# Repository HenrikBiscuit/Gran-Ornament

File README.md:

# Gran Ornament

A small, rechargeable, two-sided LED Christmas ornament. Twenty warm-white LEDs in seven channels (three rows per side and a shared star) play slow and calm light: steady high or low, a slow breath, or a flickering candle. One button turns it on, it fades in and out, switches itself off after four hours, and sleeps quietly between Christmases.

Made by hand in small batches in Denmark. This repository is the open build log: hardware, firmware, and the notes behind the decisions.

> **Status:** 🛠 Prototyping. First batch of Rev 1 boards ordered. Firmware runs on a dev board: four light modes, button, Standby, auto-off, battery compensation and low-battery cutoff. Nothing here is production-ready yet.

<!-- Add a photo here once you have one:  -->

## Using it

| Do this | What happens |
|---|---|
| Press the button | It fades in, in the mode it had last time (high if the battery has been disconnected) |
| Short press | Next mode: high → low → breathe → candle |
| Hold for 1.5 s | It fades out and switches off |
| Leave it on | It fades out and switches off by itself after 4 hours |
| Battery runs low | It fades out, pulses softly three times ("charge me") and switches off |
| Charge | USB-C |

The brightness stays the same while the battery drains, down to the 3.6 V cutoff.

## What's in here

| Folder | Contents |
|---|---|
| [`hardware/`](hardware/) | KiCad project, datasheet links, fabrication outputs (Gerbers, BOM, CPL). Each ordered revision is a [Release](../../releases), e.g. [`hw-v1`](../../releases/tag/hw-v1) |
| [`firmware/`](firmware/) | STM32G030 firmware. Runs on the dev board for now. How to build, test and lint: [`firmware/README.md`](firmware/README.md) |
| [`firmware/tests/`](firmware/tests/) | Host-side GoogleTest tests for the firmware logic, run in CI and by the pre-push gate |
| [`docs/`](docs/) | Design decisions, power budget, pinout, bring-up notes, images |
| `production/` | Programming and test process for each batch (not created yet) |
| [`CHANGELOG.md`](CHANGELOG.md) | What changed, per hardware and firmware version |

## Key parts (current choices)

| Function | Part | Notes |
|---|---|---|
| MCU | STM32G030F6P6 | Cortex-M0+, 64 MHz, 32 KB flash, 8 KB RAM, TSSOP-20 |
| LEDs | 20 × XL-1608WWC-06 | Warm white, 1608 metric (0603 imperial) |
| Charger | MCP73831 (SOT-23-5) | Linear single-cell Li-ion/LiPo charger, 4.20 V variant, 100 mA, USB-C input |
| Protection | DW01A + FS8205A | Over-discharge, over-charge and over-current protection on the board |
| Regulator | TPS7A0233 | 3.3 V LDO, ~25 nA quiescent current |
| Button | Alps SKRTLAE010 | Side-push SMD tact switch |
| Battery | Single-cell LiPo, 250 mAh planned | Cell size *TBD* (DD-002) |

Full design rationale: [`docs/design-decisions.md`](docs/design-decisions.md)

## Design goals

1. **Works next Christmas.** Every choice favours longevity: deep sleep, over-discharge protection, a battery that survives 11 months in a box.
2. **Calm light.** Gamma-corrected, high-resolution, flicker-free PWM. Nothing jumpy, nothing "disco".
3. **Safe to hang where children and pets are.** LiPo safety and robustness are requirements.
4. **Buildable by one or two people** in batches of about 150.

## Roadmap

- [x] Initial KiCad schematic
- [x] Dev board bring-up: PWM on all 7 channels, button, Standby and wake
- [x] Light modes: high, low, breathe, candle
- [x] Battery measurement, brightness compensation and low-battery cutoff (DD-011)
- [x] Fade in and out when switching on and off
- [x] PCB layout and fabrication files (Rev 1)
- [x] First batch of Rev 1 boards ordered
- [ ] Measure Standby current on the dev board
- [ ] Gamma-corrected brightness (smooth fades at the dim end)
- [ ] Stay off when a battery is first connected (saves ~100 mAh, see the power budget)
- [ ] VDD via VREFINT (battery reading stays accurate below ~3.4 V)
- [ ] First prototype boards (Rev 1) built and brought up
- [ ] Power budget measured against calculated
- [ ] Production test jig
- [ ] Compliance groundwork (CE, GPSR, Battery Regulation)

Open tasks are tracked in [Issues](../../issues).

## Licence

Gran Ornament is **source-available for non-commercial use**. You're welcome to build one for yourself, as a gift, or with a school or makerspace, and to share improvements.

**Selling it requires permission.** That covers selling assembled ornaments, kits, or boards made from these files. Get in touch at *henrik@smitt.dk* and we'll work something out.

| What | Licence |
|---|---|
| Hardware (`hardware/`), documentation and images (`docs/`) | [CC BY-NC-SA 4.0](LICENSE-CC-BY-NC-SA) |
| Firmware (`firmware/`) | [PolyForm Noncommercial 1.0.0](LICENSE) |

The name "Gran Ornament" and any logo are not covered by these licences. Please don't use them for your own builds.

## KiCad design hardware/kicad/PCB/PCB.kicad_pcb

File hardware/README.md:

# Hardware

## Layout

| Path | What goes here |
|---|---|
| `kicad/` | The KiCad project (`.kicad_pro`, `.kicad_sch`, `.kicad_pcb`) plus project-local symbol and footprint libraries |
| `kicad/lib/` | Custom symbols (`.kicad_sym`) and footprints (`.pretty/`) used by this project only |
| `fabrication/<rev>/` | Exported Gerbers, drill files, BOM and CPL for each board revision sent to the assembler |
| `datasheets/` | Links to the datasheets of every part on the board |

## Revisions

| Rev | Date | Status | Notes |
|---|---|---|---|
| Rev 1 | 2026-10 | First batch ordered ([`fabrication/Rev1/`](fabrication/Rev1/)) | First design. JLCPCB assembly |

Each revision that is sent to fabrication gets a Git tag (`hw-v1`, `hw-v2`, ...) and a
GitHub Release with the fabrication zip attached, so it is always possible to see exactly
what was built.

## Viewing without KiCad

A PDF export of the schematic lives in `docs/schematic-revX.pdf` (File → Plot in the
schematic editor). Re-export it whenever the schematic changes meaningfully, so visitors
can follow along without installing KiCad.

## Before a design leaves the house

- [ ] ERC clean (or every remaining warning explained in a comment)
- [ ] DRC clean against the assembler's design rules
- [ ] Every part has an LCSC/manufacturer part number field
- [ ] BOM and CPL exported and spot-checked for rotation
- [ ] Title block: revision and date updated, no private address
- [ ] Schematic PDF exported to `docs/`
- [ ] Tagged `hw-vX` and fabrication zip attached to a Release

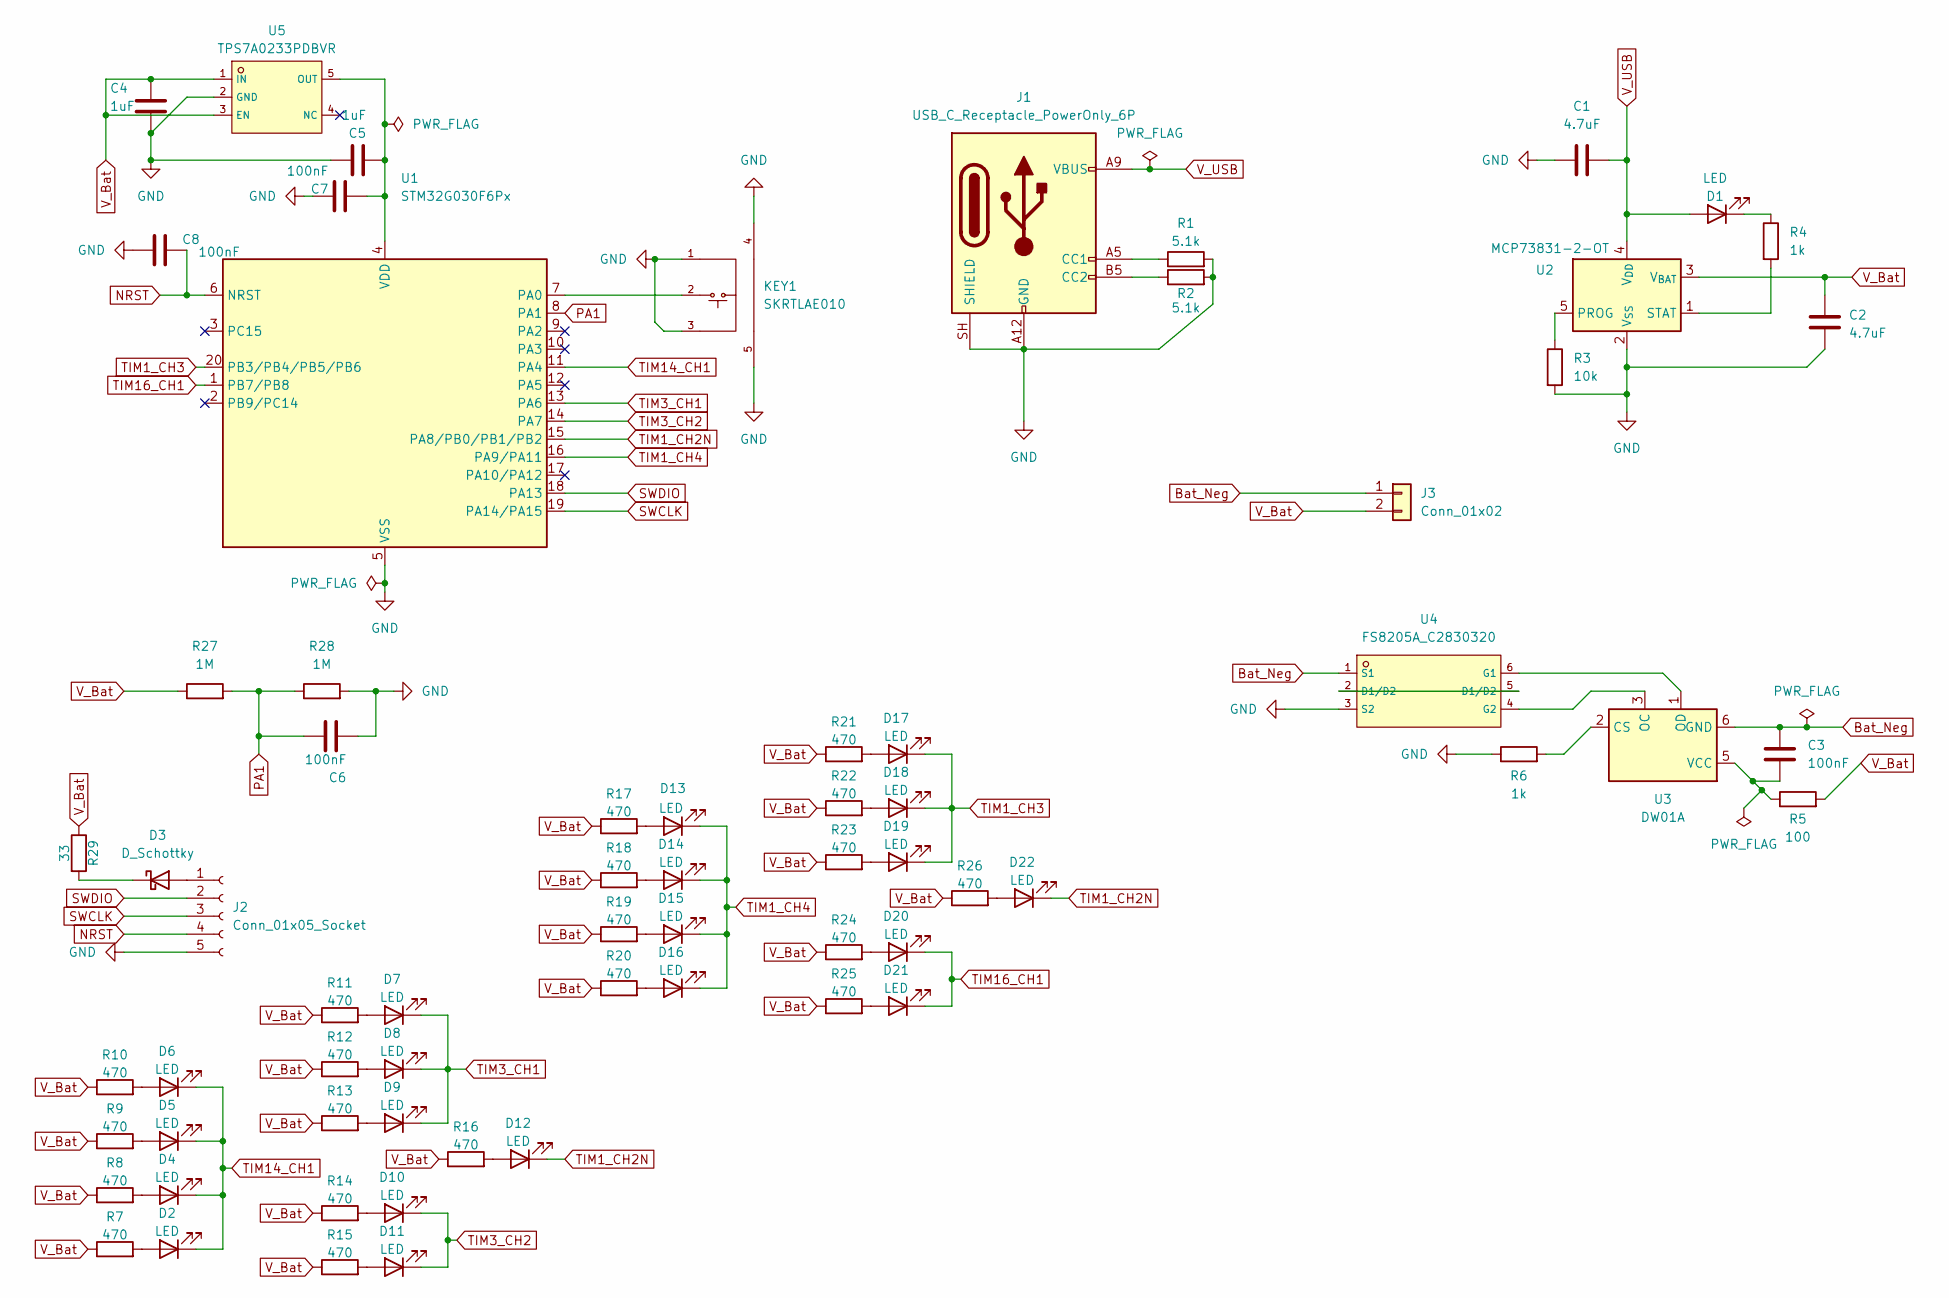
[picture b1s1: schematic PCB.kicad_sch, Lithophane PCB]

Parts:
C1, C2: 4.7uF; C_0603_1608Metric; LCSC C19666
C3, C6, C7, C8: 100nF; C_0603_1608Metric; LCSC C1591
C4, C5: 1uF; C_0603_1608Metric; LCSC C15849
D1: LED; D_0603_1608Metric; LCSC C2286
D2, D4, D5, D6, D7, D8, D9, D10, D11, D12, D13, D14, D15, D16, D17, D18, D19, D20, D21, D22: LED; D_0603_1608Metric; LCSC C965810
D3: D_Schottky; D_SOD-123; LCSC C8598
J1: USB_C_Receptacle_PowerOnly_6P; USB_C_Receptacle_GCT_USB4125-xx-x-0190_6P_TopMnt_Horizontal; LCSC C456012
J2: Conn_01x05_Socket; HDR-SMD_5P-P2.54-H-M-W12.8-N; LCSC C46061678
J3: Conn_01x02; Molex_PicoBlade_53261-0271_1x02-1MP_P1.25mm_Horizontal; LCSC C177225
KEY1: SKRTLAE010; KEY-SMD_SKRTLAE010; LCSC C110293
R1, R2: 5.1k; R_0603_1608Metric; LCSC C23186
R3: 10k; R_0603_1608Metric; LCSC C25804
R4, R6: 1k; R_0603_1608Metric; LCSC C21190
R5: 100; R_0603_1608Metric; LCSC C22775
R7, R8, R9, R10, R11, R12, R13, R14, R15, R16, R17, R18, R19, R20, R21, R22, R23, R24, R25, R26: 470; R_0603_1608Metric; LCSC C23179
R27, R28: 1M; R_0603_1608Metric; LCSC C22935
R29: 33; R_0603_1608Metric; LCSC C23140
U1: STM32G030F6Px; TSSOP-20_4.4x6.5mm_P0.65mm; LCSC C529330
U2: MCP73831-2-OT; SOT-23-5; LCSC C424093
U3: DW01A; SOT-23-6; LCSC C351410
U4: FS8205A_C2830320; SOT-23-6_L2.9-W1.6-P0.95-LS2.8-BR; LCSC C2830320
U5: TPS7A0233PDBVR; SOT-23-5_L2.9-W1.6-P0.95-LS2.8-BR; LCSC C2887324

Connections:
Bat_Neg: C3.1, J3.1, U3.6 (GND), U4.1 (S1)
GND: C1.1, C2.2, C4.2, C5.1, C6.2, C7.1, C8.2, J1.A12 (GND), J1.B12 (GND), J1.SH (SHIELD), J2.5, KEY1.1, KEY1.3, KEY1.4, KEY1.5, R1.2, R2.2, R3.2, R6.1, R28.2, U1.5 (VSS), U2.2 (V_{SS}), U4.3 (S2), U5.2 (GND)
NRST: C8.1, J2.4, U1.6 (NRST)
unnamed: D1.1 (K), R4.1
unnamed: D2.2 (A), R7.2
unnamed: D3.2 (A), J2.1
unnamed: D3.1 (K), R29.2
unnamed: D4.2 (A), R8.2
unnamed: D5.2 (A), R9.2
unnamed: D6.2 (A), R10.2
unnamed: D7.2 (A), R11.2
unnamed: D8.2 (A), R12.2
unnamed: D9.2 (A), R13.2
unnamed: D10.2 (A), R14.2
unnamed: D11.2 (A), R15.2
unnamed: D12.2 (A), R16.2
unnamed: D13.2 (A), R17.2
unnamed: D14.2 (A), R18.2
unnamed: D15.2 (A), R19.2
unnamed: D16.2 (A), R20.2
unnamed: D17.2 (A), R21.2
unnamed: D18.2 (A), R22.2
unnamed: D19.2 (A), R23.2
unnamed: D20.2 (A), R24.2
unnamed: D21.2 (A), R25.2
unnamed: D22.2 (A), R26.2
unnamed: J1.A5 (CC1), R1.1
unnamed: J1.B5 (CC2), R2.1
unnamed: KEY1.2, U1.7 (PA0)
unnamed: C5.2, C7.2, U1.4 (VDD), U5.5 (OUT)
unnamed: R3.1, U2.5 (PROG)
unnamed: R4.2, U2.1 (STAT)
unnamed: R6.2, U3.2 (CS)
unnamed: U3.3 (OC), U4.4 (G2)
unnamed: U3.1 (OD), U4.6 (G1)
unnamed: C3.2, R5.1, U3.5 (VCC)
unnamed: U4.2 (D1/D2), U4.5 (D1/D2)
PA1: C6.1, R27.2, R28.1, U1.8 (PA1)
SWCLK: J2.3, U1.19 (PA14/PA15)
SWDIO: J2.2, U1.18 (PA13)
TIM1_CH2N: D12.1 (K), D22.1 (K), U1.15 (PA8/PB0/PB1/PB2)
TIM1_CH3: D17.1 (K), D18.1 (K), D19.1 (K), U1.20 (PB3/PB4/PB5/PB6)
TIM1_CH4: D13.1 (K), D14.1 (K), D15.1 (K), D16.1 (K), U1.16 (PA9/PA11)
TIM3_CH1: D7.1 (K), D8.1 (K), D9.1 (K), U1.13 (PA6)
TIM3_CH2: D10.1 (K), D11.1 (K), U1.14 (PA7)
TIM14_CH1: D2.1 (K), D4.1 (K), D5.1 (K), D6.1 (K), U1.11 (PA4)
TIM16_CH1: D20.1 (K), D21.1 (K), U1.1 (PB7/PB8)
V_Bat: C2.1, C4.1, J3.2, R5.2, R7.1, R8.1, R9.1, R10.1, R11.1, R12.1, R13.1, R14.1, R15.1, R16.1, R17.1, R18.1, R19.1, R20.1, R21.1, R22.1, R23.1, R24.1, R25.1, R26.1, R27.1, R29.1, U2.3 (V_{BAT}), U5.1 (IN), U5.3 (EN)
V_USB: C1.2, D1.2 (A), J1.A9 (VBUS), J1.B9 (VBUS), U2.4 (V_{DD})

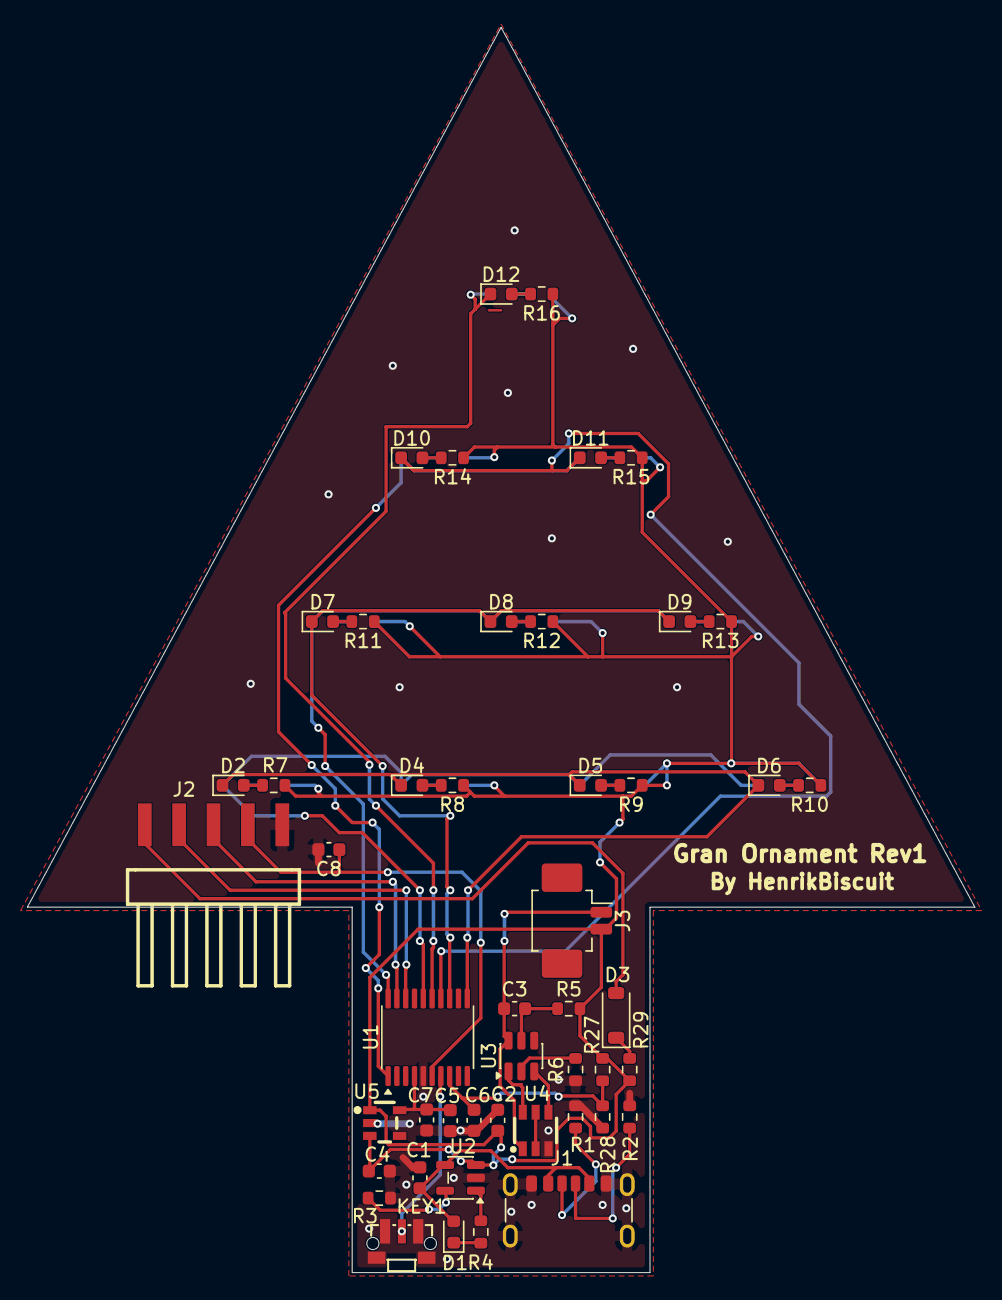
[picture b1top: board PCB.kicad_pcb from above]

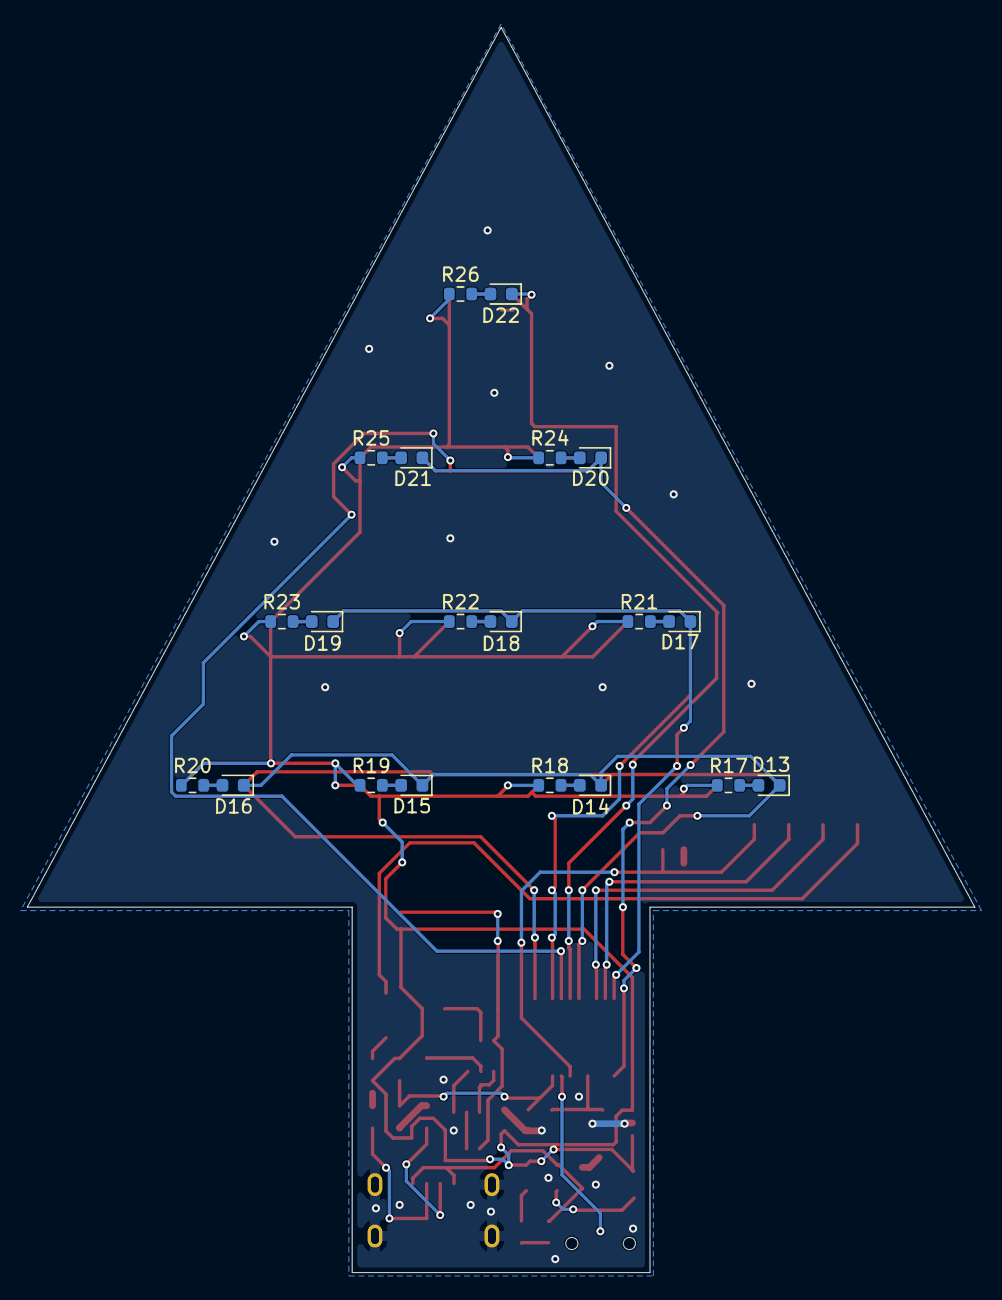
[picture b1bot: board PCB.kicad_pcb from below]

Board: 2 copper layers, 70.0 x 92.0 mm, 68 parts (20 on the bottom side), 49 nets.

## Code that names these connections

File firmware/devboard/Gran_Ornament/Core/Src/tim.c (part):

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    __HAL_RCC_GPIOB_CLK_ENABLE();
    __HAL_RCC_GPIOA_CLK_ENABLE();
    /**TIM1 GPIO Configuration
    PB0     ------> TIM1_CH2N
    PA11 [PA9]     ------> TIM1_CH4
    PB6     ------> TIM1_CH3
    */
    GPIO_InitStruct.Pin = GPIO_PIN_0;
    GPIO_InitStruct.Mode = GPIO_MODE_AF_OD;
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
    __HAL_RCC_GPIOA_CLK_ENABLE();
    /**TIM3 GPIO Configuration
    PA6     ------> TIM3_CH1
    PA7     ------> TIM3_CH2
    */
    GPIO_InitStruct.Pin = GPIO_PIN_6|GPIO_PIN_7;
    GPIO_InitStruct.Mode = GPIO_MODE_AF_OD;
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
    __HAL_RCC_GPIOA_CLK_ENABLE();
    /**TIM14 GPIO Configuration
    PA4     ------> TIM14_CH1
    */
    GPIO_InitStruct.Pin = GPIO_PIN_4;
    GPIO_InitStruct.Mode = GPIO_MODE_AF_OD;
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
    __HAL_RCC_GPIOB_CLK_ENABLE();
    /**TIM16 GPIO Configuration
    PB8     ------> TIM16_CH1
    */
    GPIO_InitStruct.Pin = GPIO_PIN_8;
    GPIO_InitStruct.Mode = GPIO_MODE_AF_OD;
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

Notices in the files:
firmware/devboard/Gran_Ornament/Core/Src/tim.c:
Copyright (c) 2026 STMicroelectronics.
All rights reserved.
This software is licensed under terms that can be found in the LICENSE file
